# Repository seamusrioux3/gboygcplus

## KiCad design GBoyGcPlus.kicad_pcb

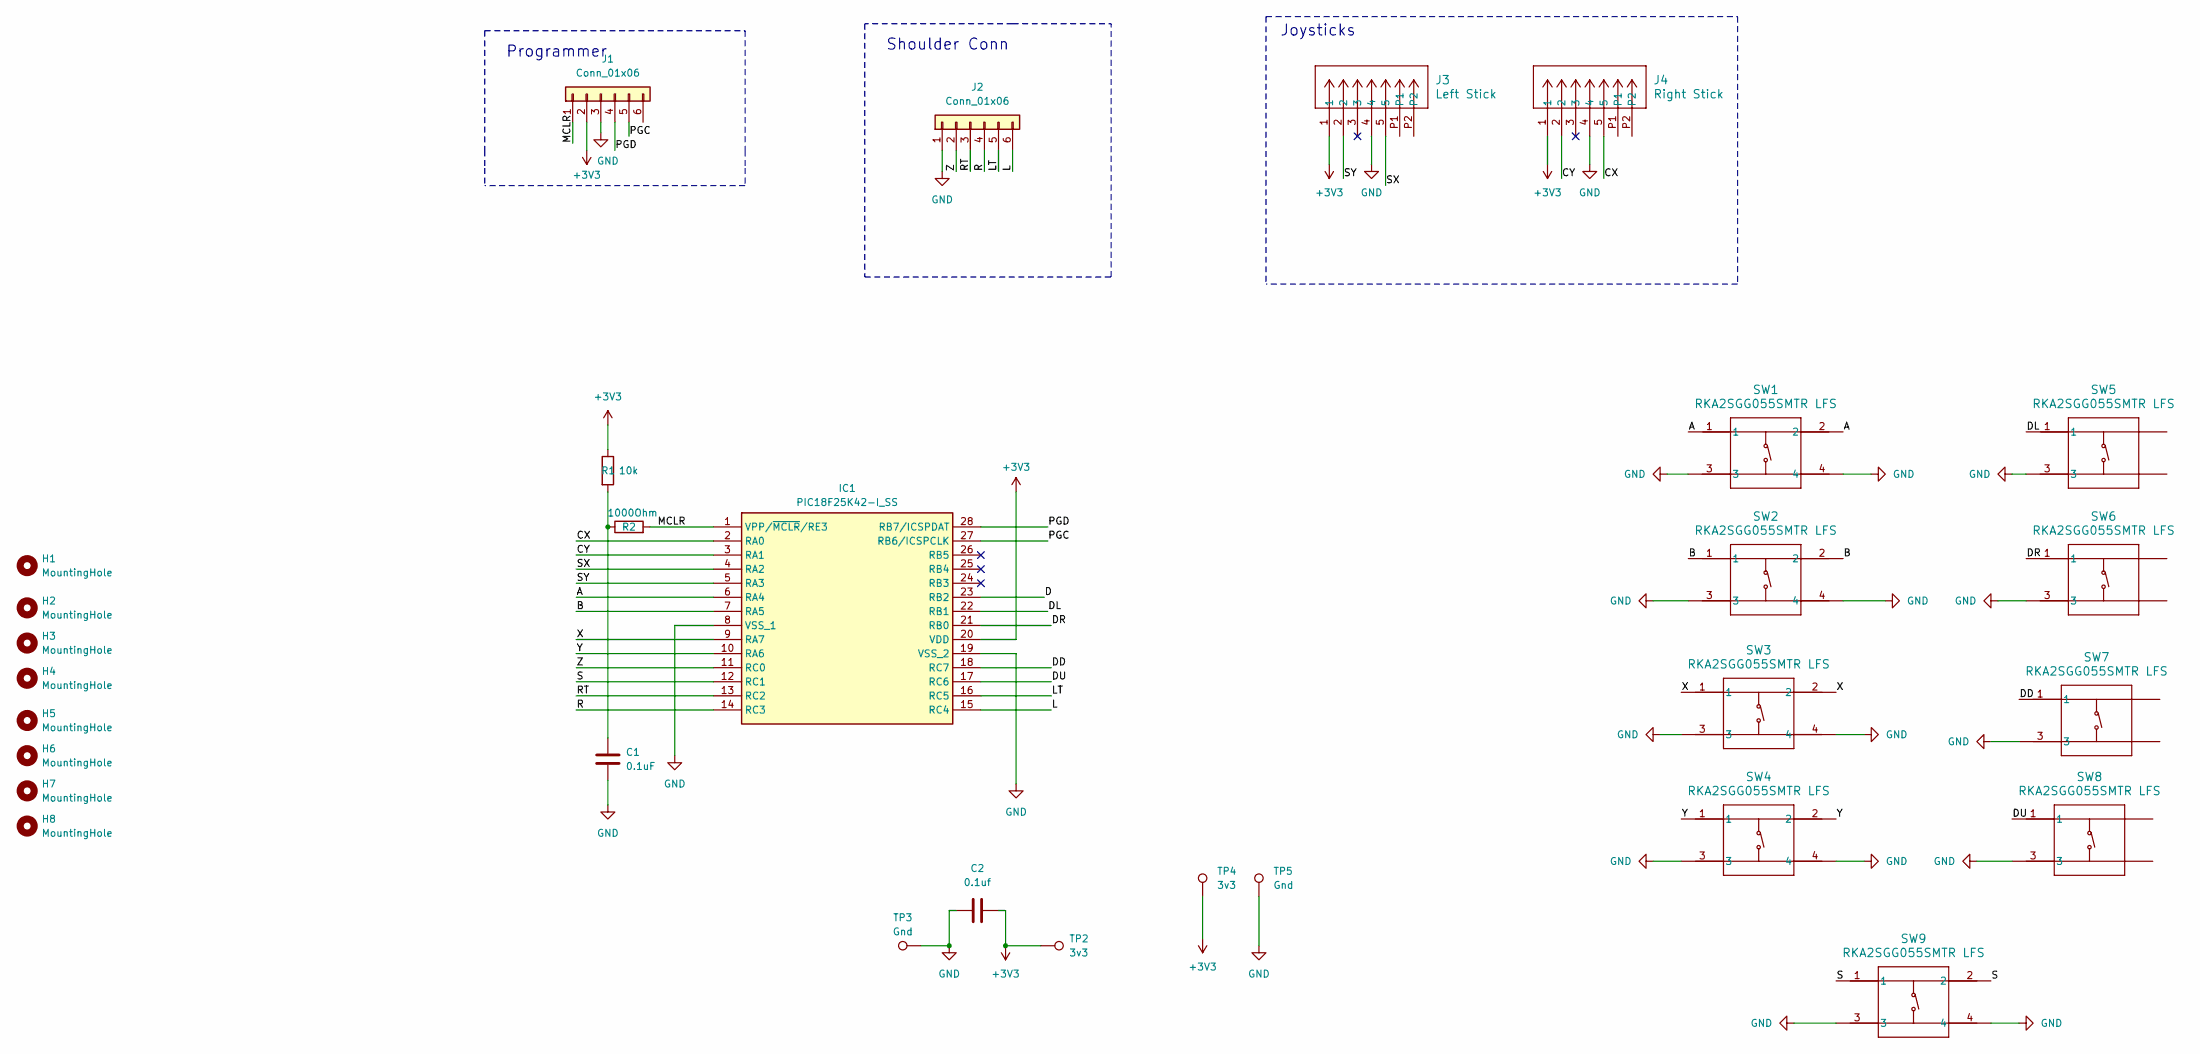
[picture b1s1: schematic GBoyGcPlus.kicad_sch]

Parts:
C1: 0.1uF; C_0402_1005Metric
C2: 0.1uf; C_0402_1005Metric
H1, H2, H3, H4, H5, H6, H7, H8: MountingHole; MountingHole_2.2mm_M2
IC1: PIC18F25K42-I_SS; SOP65P780X200-28N; Mouser Part Number 579-PIC18F25K42-I/SS
J1, J2: Conn_01x06; PinSocket_1x06_P1.27mm_Vertical
J3: Left Stick; CON_5051100592_MOL
J4: Right Stick; CON_5051100592_MOL
R1: 10k; R_0402_1005Metric
R2: 1000Ohm; R_0402_1005Metric
SW1, SW2, SW3, SW4: RKA2SGG055SMTR LFS; ABXY
SW5, SW6, SW7, SW8: RKA2SGG055SMTR LFS; DPAD
SW9: RKA2SGG055SMTR LFS; RKA2SG_CNK-L
TP2, TP4: 3v3; TestPoint_Pad_D1.0mm
TP3, TP5: Gnd; TestPoint_Pad_D1.0mm

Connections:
+3V3: C2.2, IC1.20 (VDD), J1.2, J3.1, J4.1, R1.1, TP2.1, TP4.1
/A: IC1.6 (RA4), SW1.1, SW1.2
/B: IC1.7 (RA5), SW2.1, SW2.2
/CX: IC1.2 (RA0), J4.5
/CY: IC1.3 (RA1), J4.2
/D: IC1.23 (RB2)
/DD: IC1.18 (RC7), SW7.1
/DL: IC1.22 (RB1), SW5.1
/DR: IC1.21 (RB0), SW6.1
/DU: IC1.17 (RC6), SW8.1
/L: IC1.15 (RC4), J2.6
/LT: IC1.16 (RC5), J2.5
/MCLR: IC1.1 (VPP/~MCLR/RE3), J1.1, R2.2
/PGC: IC1.27 (RB6/ICSPCLK), J1.5
/PGD: IC1.28 (RB7/ICSPDAT), J1.4
/R: IC1.14 (RC3), J2.4
/RT: IC1.13 (RC2), J2.3
/S: IC1.12 (RC1), SW9.1, SW9.2
/SX: IC1.4 (RA2), J3.5
/SY: IC1.5 (RA3), J3.2
/X: IC1.9 (RA7), SW3.1, SW3.2
/Y: IC1.10 (RA6), SW4.1, SW4.2
/Z: IC1.11 (RC0), J2.2
GND: C1.2, C2.1, IC1.8 (VSS_1), IC1.19 (VSS_2), J1.3, J2.1, J3.4, J4.4, SW1.3, SW1.4, SW2.3, SW2.4, SW3.3, SW3.4, SW4.3, SW4.4, SW5.3, SW6.3, SW7.3, SW8.3, SW9.3, SW9.4, TP3.1, TP5.1
unnamed: C1.1, R1.2, R2.1

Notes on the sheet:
Programmer
Joysticks
Shoulder Conn

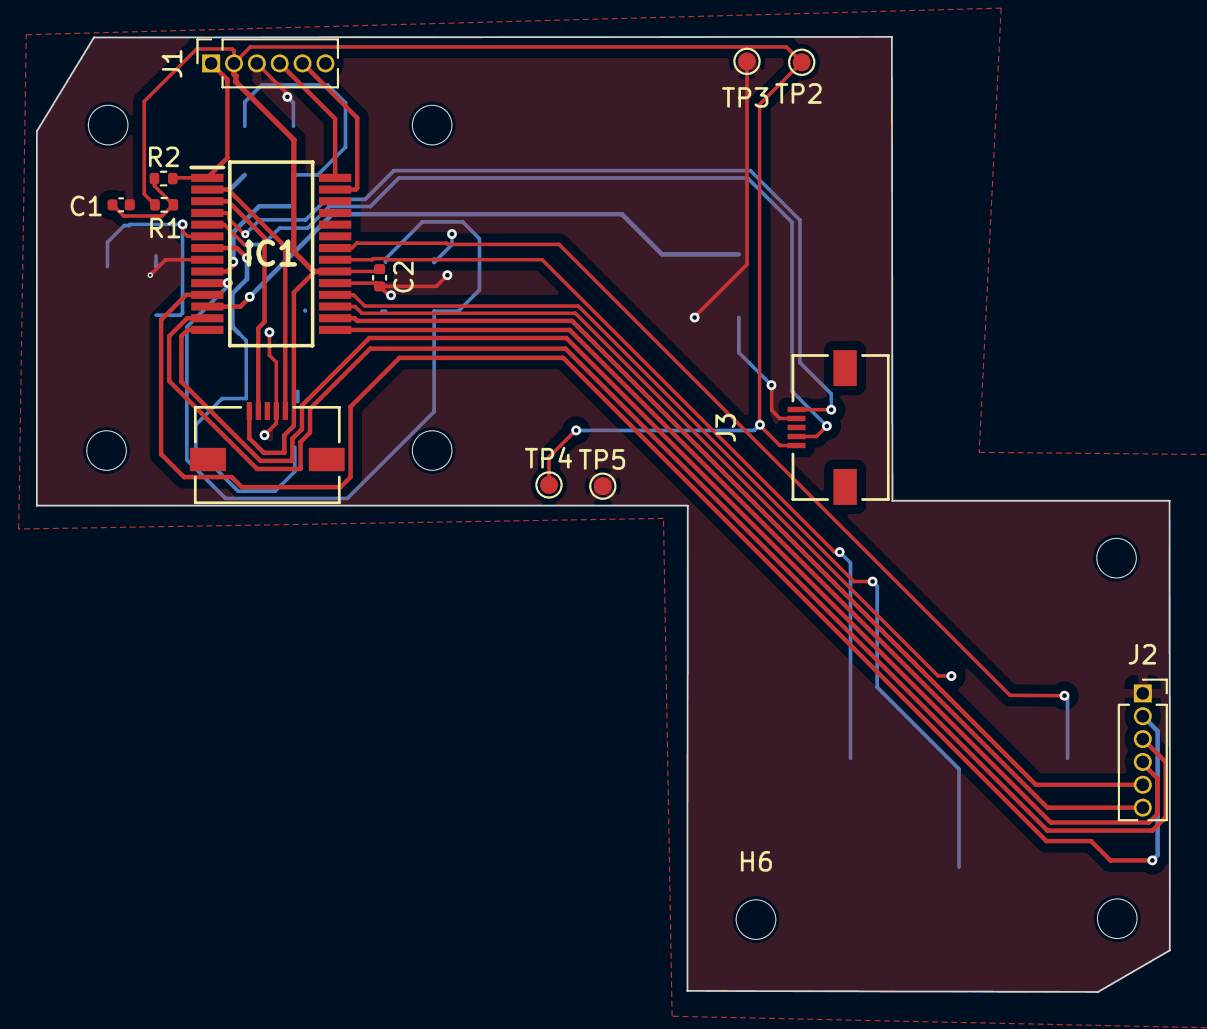
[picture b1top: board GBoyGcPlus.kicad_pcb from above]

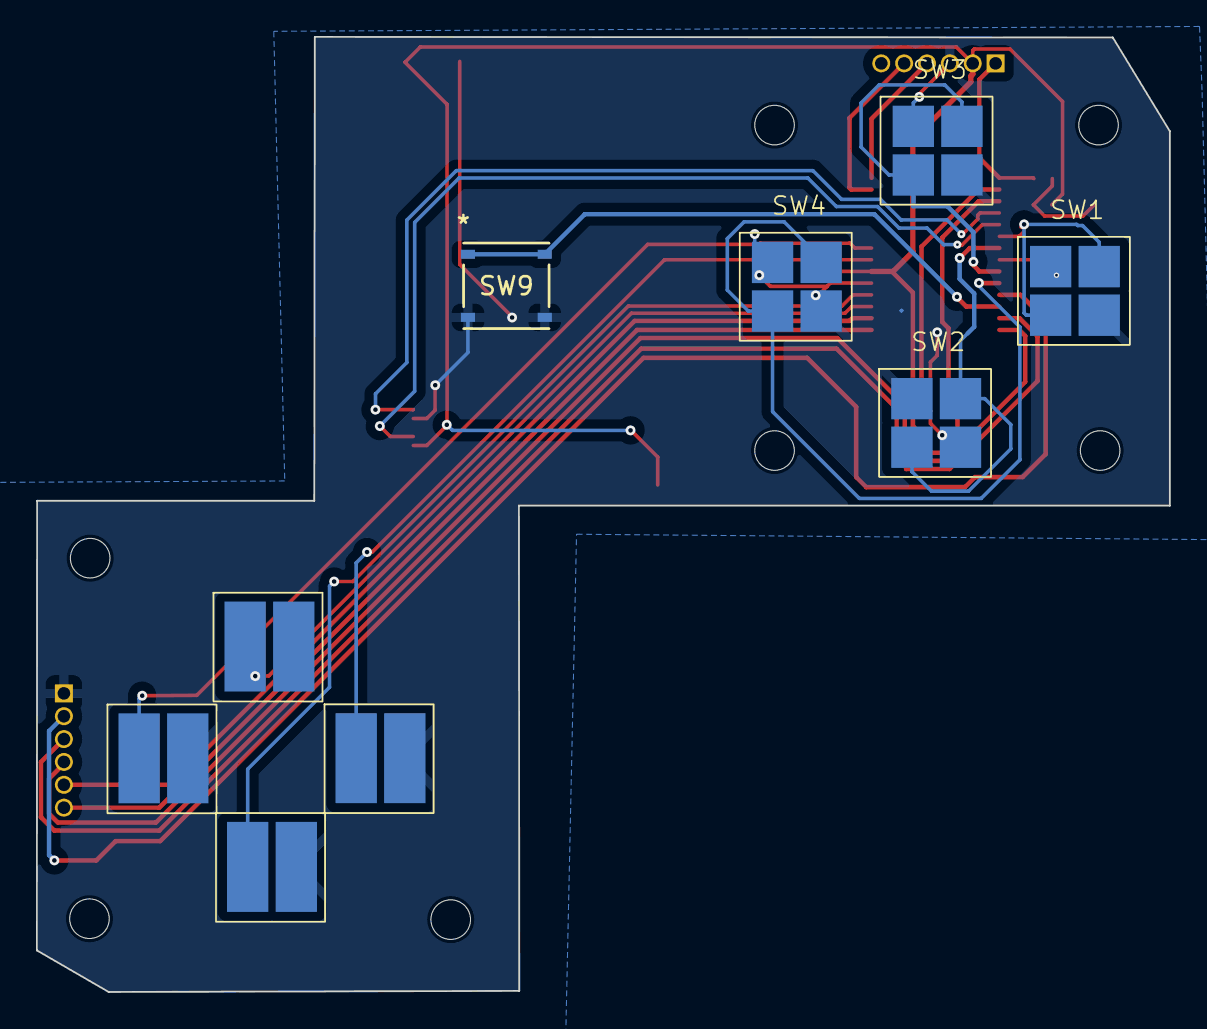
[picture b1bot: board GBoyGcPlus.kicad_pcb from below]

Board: 2 copper layers, 62.9 x 53.1 mm, 29 parts (9 on the bottom side), 24 nets.

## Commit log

2024-02-19 Added schematic and pcb file
2024-02-20 Schematic only
2024-02-21 Added gerber files
2024-02-26 Changed PCB to use GC2 Micro controller
